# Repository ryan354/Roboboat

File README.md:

# Roboboat
robotic project related to surface unmaned vehicle

there are ground station controller and main microcontroller 
the communication between GS and the robot using APC220 that use low frequency 433Mhz 

for the microcontroller i used arduino uno both in GS and roboboat

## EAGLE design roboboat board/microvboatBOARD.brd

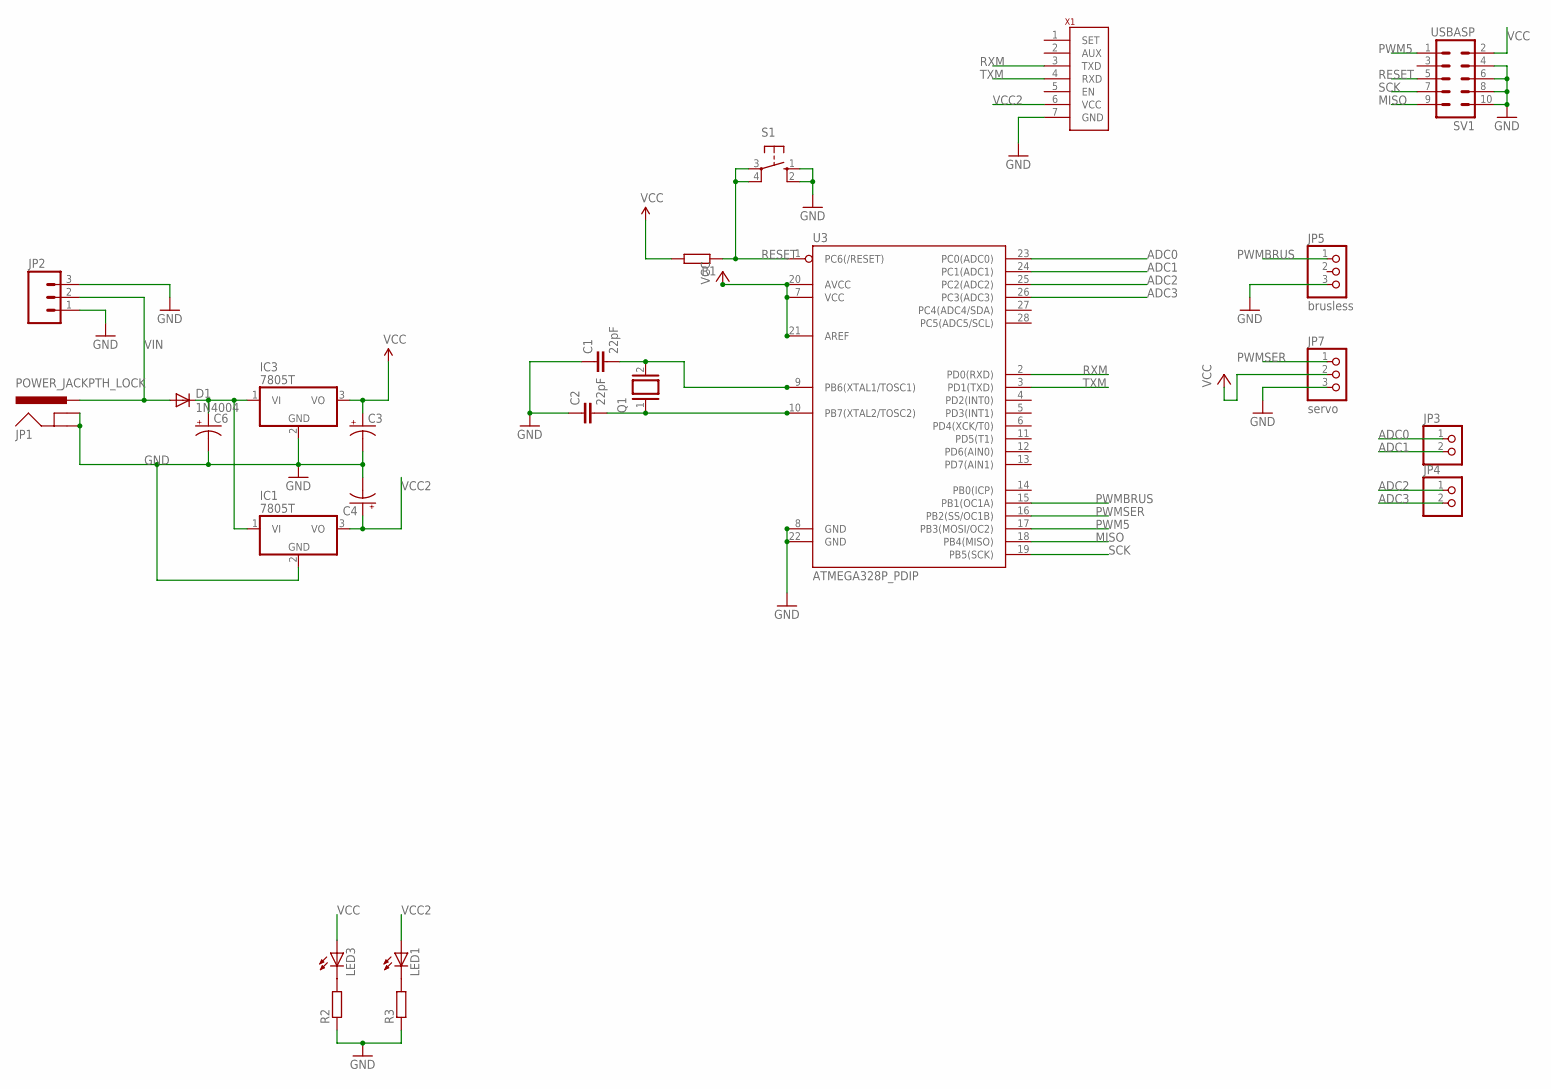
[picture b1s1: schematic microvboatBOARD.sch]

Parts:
C1, C2: 22pF; C2.5-3
C3, C4, C6: CPOL-USE2.5-5; E2,5-5
D1: 1N4004; DO41-10
IC1, IC3: 7805T; TO220H
JP1: POWER_JACKPTH_LOCK; POWER_JACK_PTH_LOCK
JP2: M03POLAR; MOLEX-1X3
JP3, JP4: PINHD-1X2; 1X02
JP5: brusless; 1X03
JP7: servo; 1X03
LED1, LED3: LED3MM
Q1: XTAL/S; QS
R1, R2, R3: R-EU_0204/7; 0204/7
S1: 10-XX; B3F-10XX
SV1: USBASP; ML10
U3: ATMEGA328P_PDIP; DIL28-3
X1: APC220

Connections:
ADC0: JP3.1, U3.23 (PC0(ADC0))
ADC1: JP3.2, U3.24 (PC1(ADC1))
ADC2: JP4.1, U3.25 (PC2(ADC2))
ADC3: JP4.2, U3.26 (PC3(ADC3))
GND: C1.1, C2.1, C3.-, C4.-, C6.-, IC1.2 (GND), IC3.2 (GND), JP1.GND, JP1.GNDBREAK, JP2.1, JP2.3, JP5.3, JP7.3, R2.1, R3.1, S1.1 (S), S1.2 (S1), SV1.4, SV1.6, SV1.8, SV1.10, U3.8 (GND), U3.22 (GND), X1.7 (GND)
MISO: SV1.9, U3.18 (PB4(MISO))
unnamed: LED3.K (C), R2.2
unnamed: C1.2, Q1.2, U3.9 (PB6(XTAL1/TOSC1))
unnamed: C2.2, Q1.1, U3.10 (PB7(XTAL2/TOSC2))
unnamed: LED1.K (C), R3.2
unnamed: C6.+, D1.C, IC1.1 (VI), IC3.1 (VI)
PWM5: SV1.1, U3.17 (PB3(MOSI/OC2))
PWMBRUS: JP5.1, U3.15 (PB1(OC1A))
PWMSER: JP7.1, U3.16 (PB2(SS/OC1B))
RESET: R1.1, S1.3, S1.4 (P1), SV1.5, U3.1 (PC6(/RESET))
RXM: U3.2 (PD0(RXD)), X1.3 (TXD)
SCK: SV1.7, U3.19 (PB5(SCK))
TXM: U3.3 (PD1(TXD)), X1.4 (RXD)
VCC: C3.+, IC3.3 (VO), JP7.2, LED3.A, R1.2, SV1.2, U3.7 (VCC), U3.20 (AVCC), U3.21 (AREF)
VCC2: C4.+, IC1.3 (VO), LED1.A, X1.6 (VCC)
VIN: D1.A, JP1.PWR, JP2.2

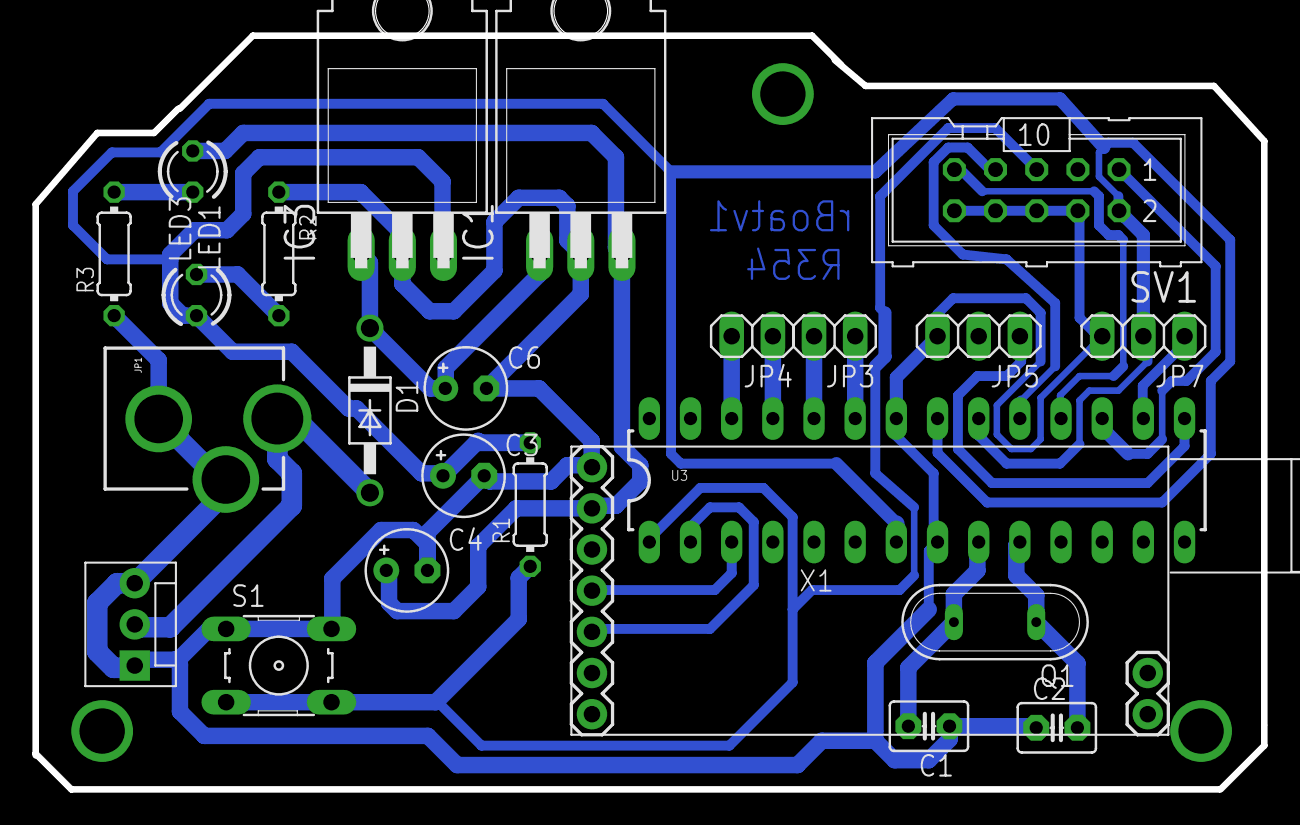
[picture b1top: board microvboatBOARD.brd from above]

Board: 2 copper layers, 75.8 x 46.5 mm, 24 parts (0 on the bottom side), 21 nets.

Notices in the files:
parts and their libraries:
SparkFun-Connectors: Licensing: Creative Commons ShareAlike 4.0 International - https://creativecommons.org/licenses/by-sa/4.0
